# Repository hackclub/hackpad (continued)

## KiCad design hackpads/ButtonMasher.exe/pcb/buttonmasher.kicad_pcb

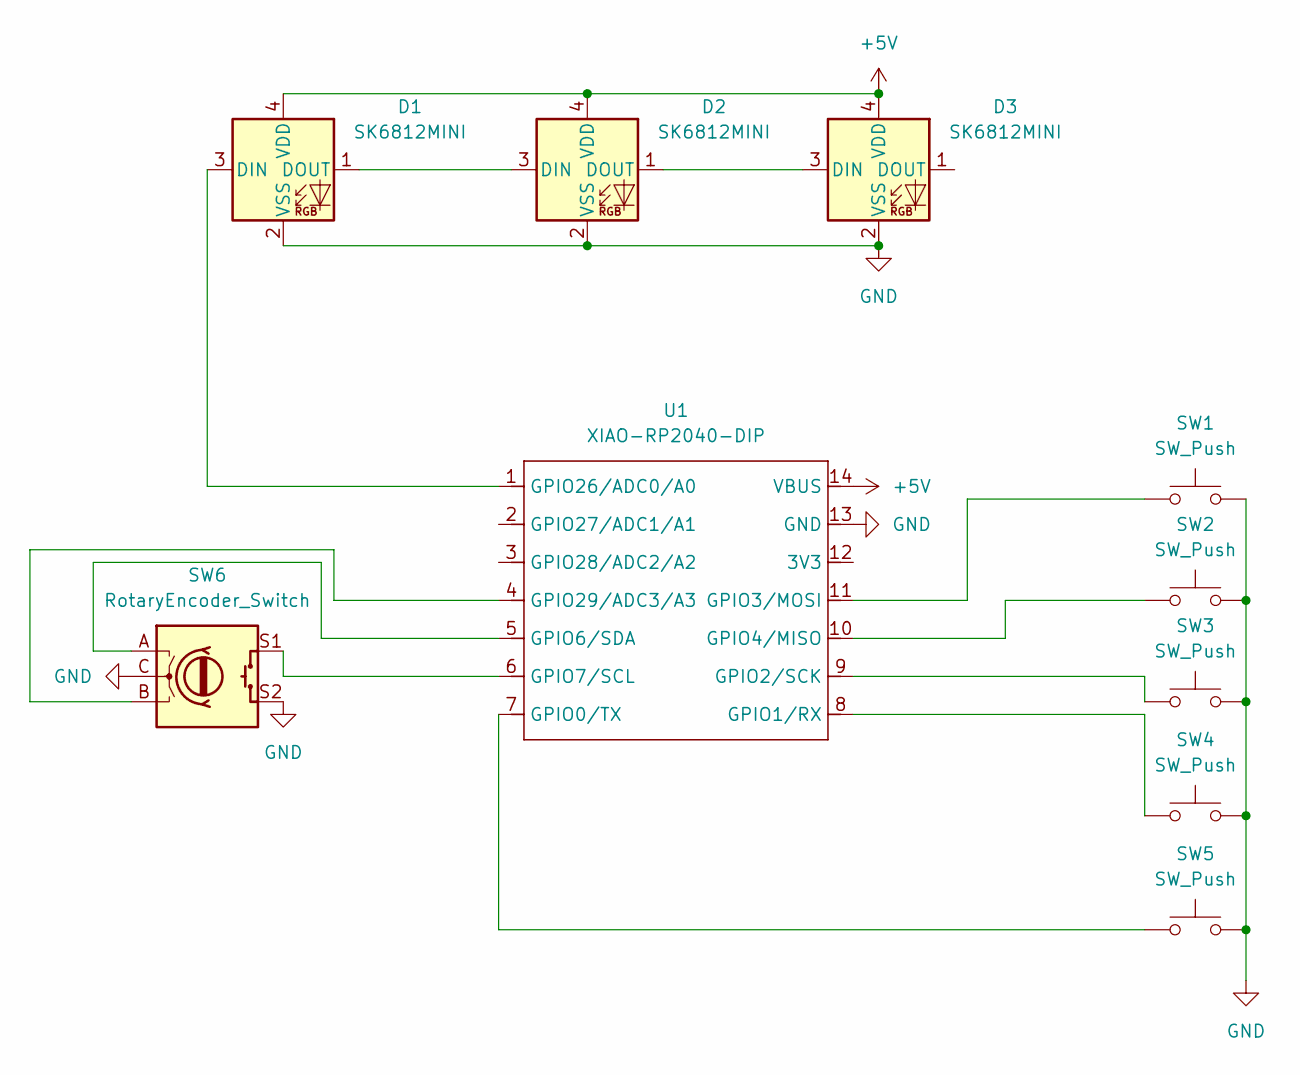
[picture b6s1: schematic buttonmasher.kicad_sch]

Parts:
D1, D2, D3: SK6812MINI; LED_SK6812MINI_PLCC4_3.5x3.5mm_P1.75mm
SW1, SW2, SW3, SW4, SW5: SW_Push; SW_Cherry_MX_1.00u_PCB
SW6: RotaryEncoder_Switch; RotaryEncoder_Alps_EC11E-Switch_Vertical_H20mm_CircularMoun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
U1: XIAO-RP2040-DIP

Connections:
+5V: D1.4 (VDD), D2.4 (VDD), D3.4 (VDD), U1.14 (VBUS)
GND: D1.2 (VSS), D2.2 (VSS), D3.2 (VSS), SW1.2, SW2.2, SW3.2, SW4.2, SW5.2, SW6.C, SW6.S2, U1.13 (GND)
unnamed: D1.3 (DIN), U1.1 (GPIO26/ADC0/A0)
unnamed: D1.1 (DOUT), D2.3 (DIN)
unnamed: D2.1 (DOUT), D3.3 (DIN)
unnamed: SW5.1, U1.7 (GPIO0/TX)
unnamed: SW4.1, U1.8 (GPIO1/RX)
unnamed: SW3.1, U1.9 (GPIO2/SCK)
unnamed: SW1.1, U1.11 (GPIO3/MOSI)
unnamed: SW2.1, U1.10 (GPIO4/MISO)
unnamed: SW6.A, U1.5 (GPIO6/SDA)
unnamed: SW6.S1, U1.6 (GPIO7/SCL)
unnamed: SW6.B, U1.4 (GPIO29/ADC3/A3)

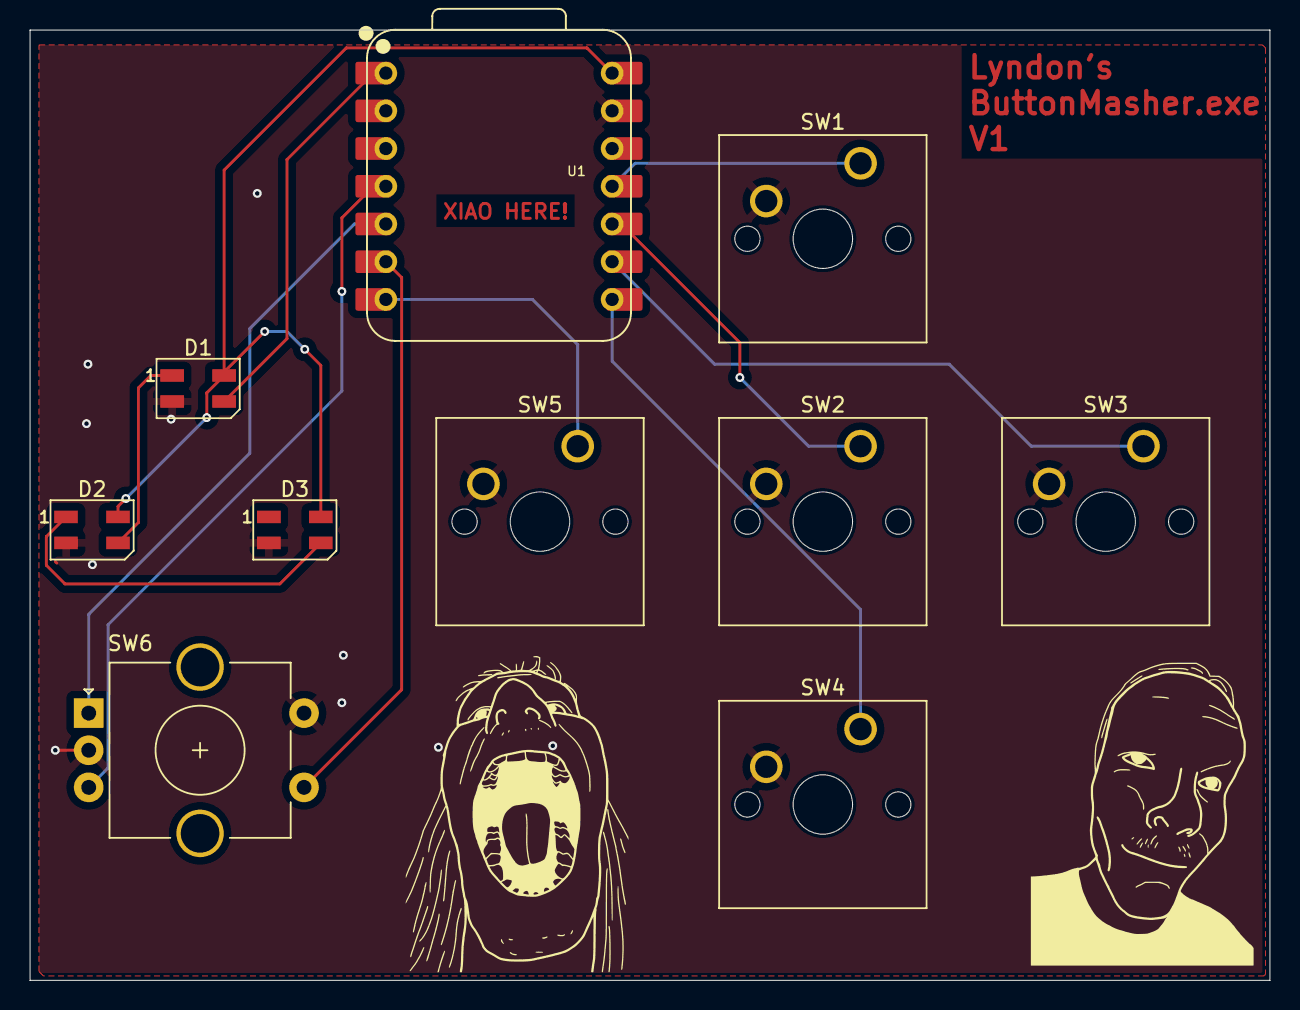
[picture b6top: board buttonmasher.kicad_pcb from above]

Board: 2 copper layers, 83.5 x 64.0 mm, 10 parts (0 on the bottom side), 13 nets.

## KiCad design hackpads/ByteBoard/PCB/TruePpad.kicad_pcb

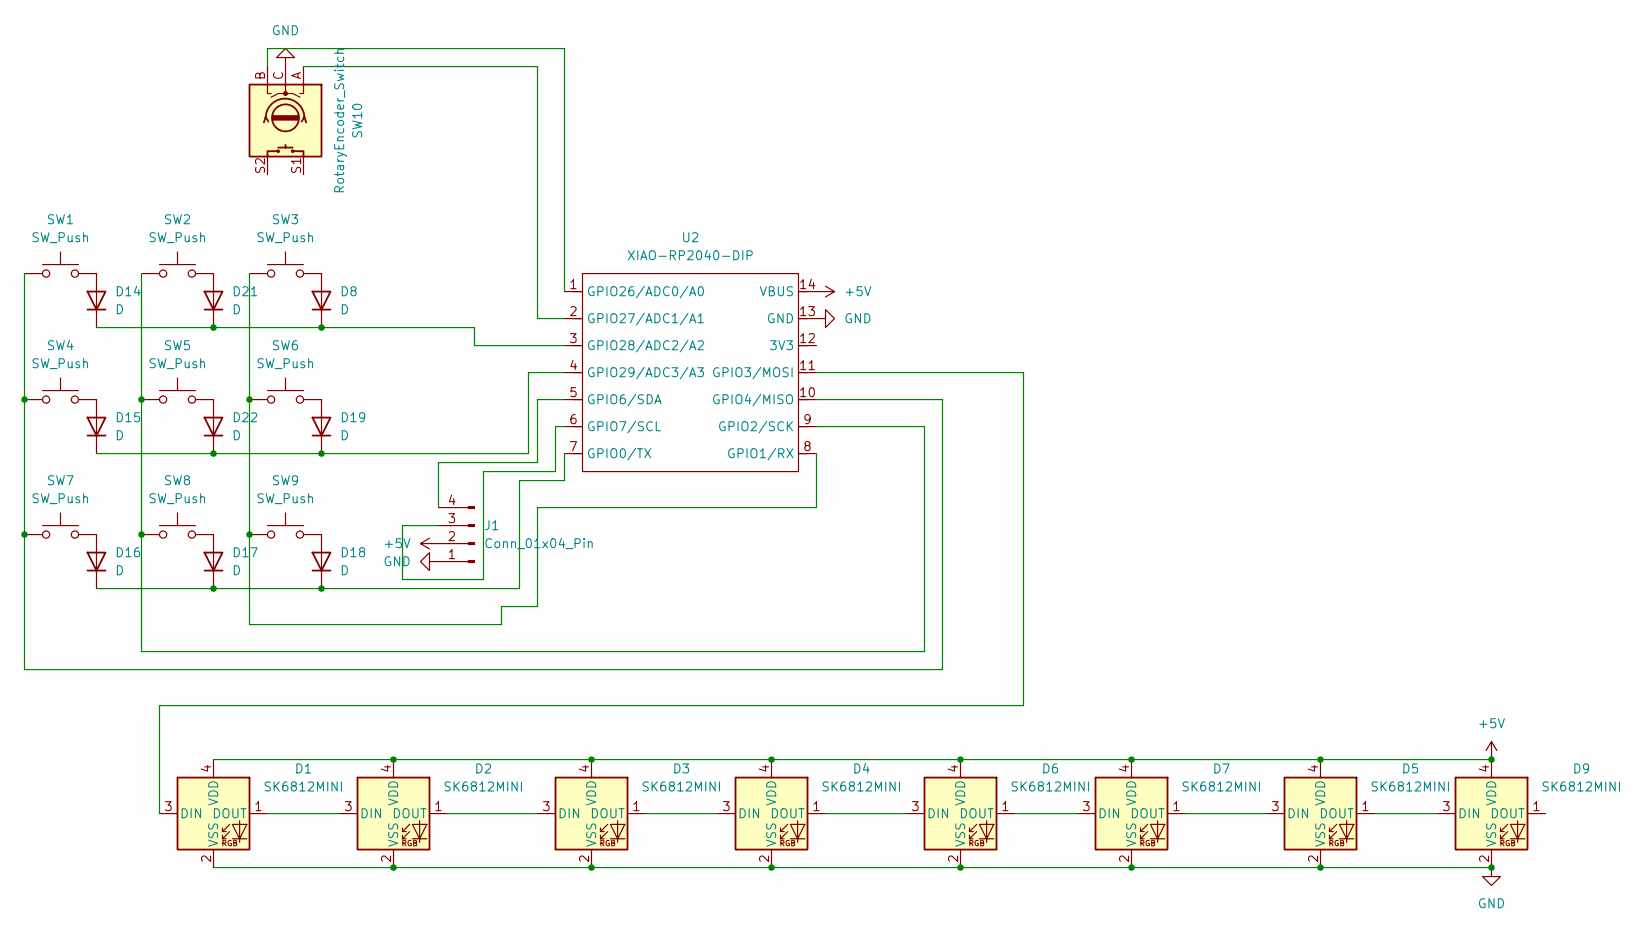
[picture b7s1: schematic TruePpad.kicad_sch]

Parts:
D1, D2, D3, D4, D5, D6, D7, D9: SK6812MINI; LED_SK6812MINI_PLCC4_3.5x3.5mm_P1.75mm
D8, D14, D15, D16, D17, D18, D19, D21, D22: D; D_DO-35_SOD27_P7.62mm_Horizontal
J1: Conn_01x04_Pin; SSD1306-0.91-OLED-4pin-128x32
SW1, SW2, SW3, SW4, SW5, SW6, SW7, SW8, SW9: SW_Push; SW_Cherry_MX_1.00u_PCB
SW10: RotaryEncoder_Switch; RotaryEncoder_Alps_EC11E-Switch_Vertical_H20mm_CircularMoun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
U2: XIAO-RP2040-DIP

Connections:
+5V: D1.4 (VDD), D2.4 (VDD), D3.4 (VDD), D4.4 (VDD), D5.4 (VDD), D6.4 (VDD), D7.4 (VDD), D9.4 (VDD), J1.2, U2.14 (VBUS)
GND: D1.2 (VSS), D2.2 (VSS), D3.2 (VSS), D4.2 (VSS), D5.2 (VSS), D6.2 (VSS), D7.2 (VSS), D9.2 (VSS), J1.1, SW10.C, U2.13 (GND)
unnamed: D1.3 (DIN), U2.11 (GPIO3/MOSI)
unnamed: D1.1 (DOUT), D2.3 (DIN)
unnamed: D2.1 (DOUT), D3.3 (DIN)
unnamed: D3.1 (DOUT), D4.3 (DIN)
unnamed: D4.1 (DOUT), D6.3 (DIN)
unnamed: D5.3 (DIN), D7.1 (DOUT)
unnamed: D5.1 (DOUT), D9.3 (DIN)
unnamed: D6.1 (DOUT), D7.3 (DIN)
unnamed: D8.2 (A), SW3.2
unnamed: D14.2 (A), SW1.2
unnamed: D8.1 (K), D14.1 (K), D21.1 (K), U2.3 (GPIO28/ADC2/A2)
unnamed: D15.2 (A), SW4.2
unnamed: D15.1 (K), D19.1 (K), D22.1 (K), U2.4 (GPIO29/ADC3/A3)
unnamed: D16.2 (A), SW7.2
unnamed: D16.1 (K), D17.1 (K), D18.1 (K), U2.7 (GPIO0/TX)
unnamed: D17.2 (A), SW8.2
unnamed: D18.2 (A), SW9.2
unnamed: D19.2 (A), SW6.2
unnamed: D21.2 (A), SW2.2
unnamed: D22.2 (A), SW5.2
unnamed: J1.3, U2.6 (GPIO7/SCL)
unnamed: J1.4, U2.5 (GPIO6/SDA)
unnamed: SW3.1, SW6.1, SW9.1, U2.8 (GPIO1/RX)
unnamed: SW2.1, SW5.1, SW8.1, U2.9 (GPIO2/SCK)
unnamed: SW1.1, SW4.1, SW7.1, U2.10 (GPIO4/MISO)
unnamed: SW10.B, U2.1 (GPIO26/ADC0/A0)
unnamed: SW10.A, U2.2 (GPIO27/ADC1/A1)

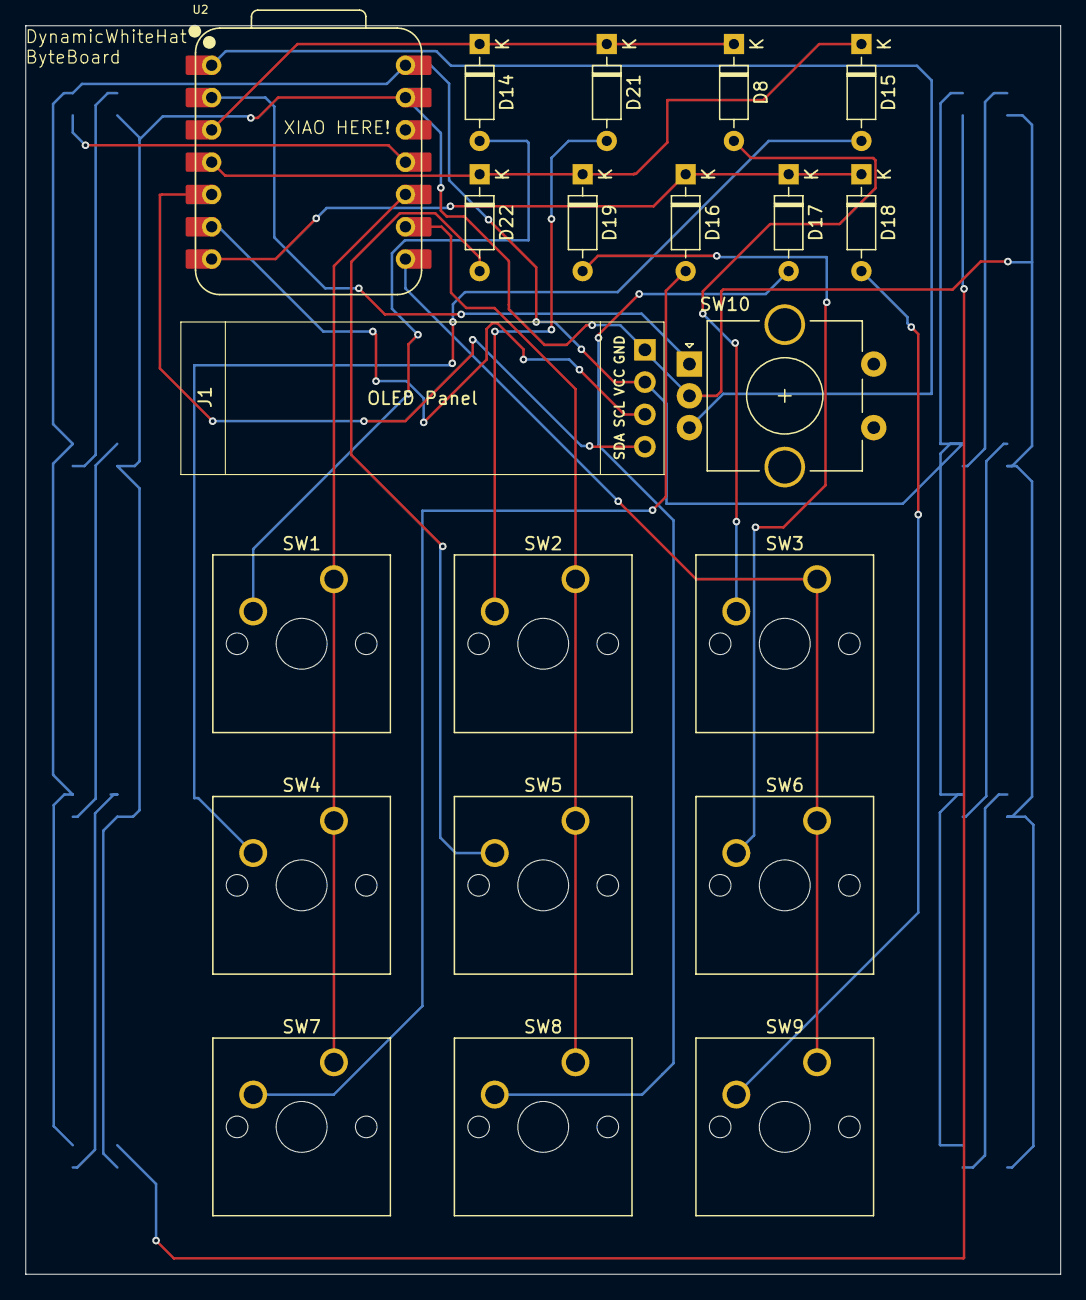
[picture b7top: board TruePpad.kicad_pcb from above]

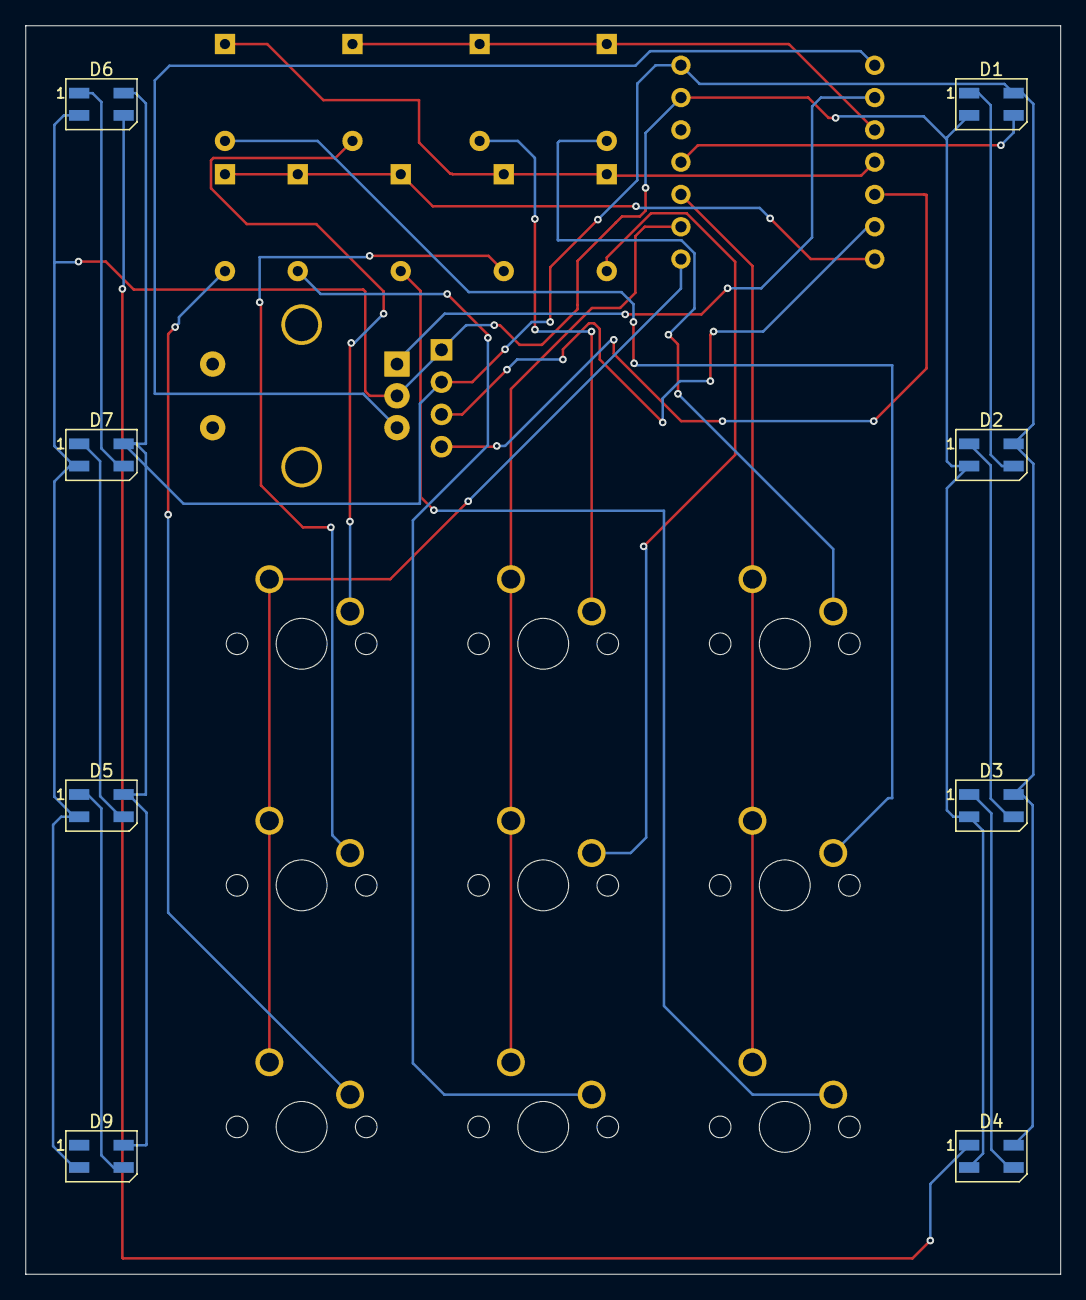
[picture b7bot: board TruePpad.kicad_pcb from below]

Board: 2 copper layers, 81.4 x 98.2 mm, 29 parts (8 on the bottom side), 29 nets.

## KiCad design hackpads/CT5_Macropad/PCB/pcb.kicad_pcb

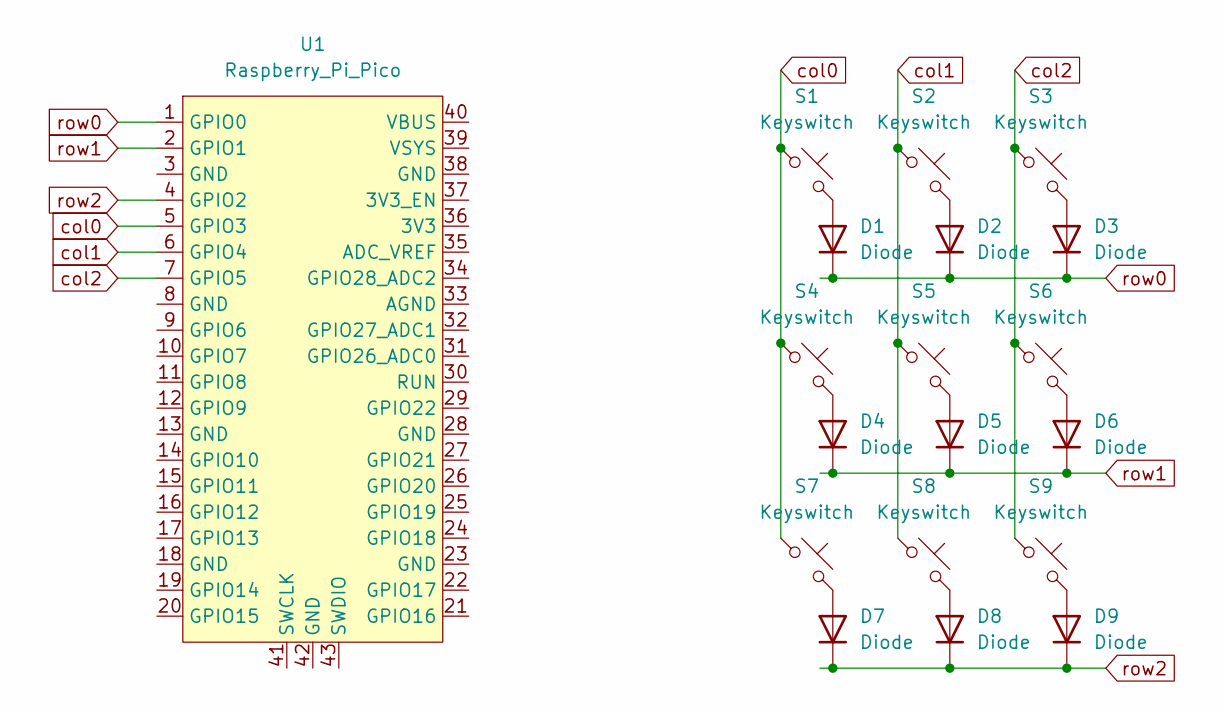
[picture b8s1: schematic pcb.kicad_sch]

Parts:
D1, D2, D3, D4, D5, D6, D7, D8, D9: Diode; Diode_DO-35
S1, S2, S3, S4, S5, S6, S7, S8, S9: Keyswitch; MX_PCB_1.00u
U1: Raspberry_Pi_Pico

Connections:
unnamed: D1.2 (A), S1.2
unnamed: D2.2 (A), S2.2
unnamed: D3.2 (A), S3.2
unnamed: D4.2 (A), S4.2
unnamed: D5.2 (A), S5.2
unnamed: D6.2 (A), S6.2
unnamed: D7.2 (A), S7.2
unnamed: D8.2 (A), S8.2
unnamed: D9.2 (A), S9.2
col0: S1.1, S4.1, S7.1, U1.5 (GPIO3)
col1: S2.1, S5.1, S8.1, U1.6 (GPIO4)
col2: S3.1, S6.1, S9.1, U1.7 (GPIO5)
row0: D1.1 (K), D2.1 (K), D3.1 (K), U1.1 (GPIO0)
row1: D4.1 (K), D5.1 (K), D6.1 (K), U1.2 (GPIO1)
row2: D7.1 (K), D8.1 (K), D9.1 (K), U1.4 (GPIO2)

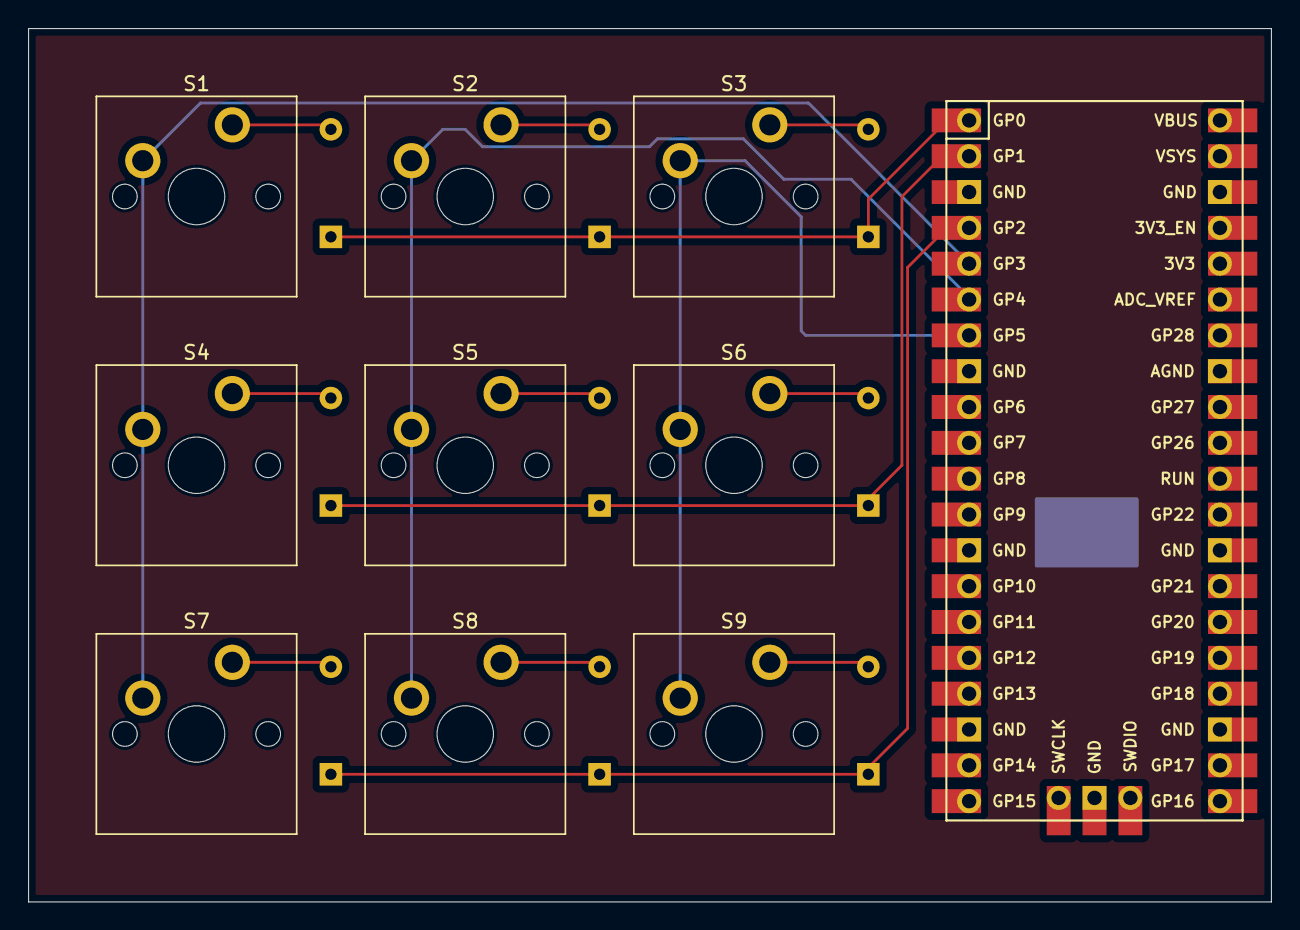
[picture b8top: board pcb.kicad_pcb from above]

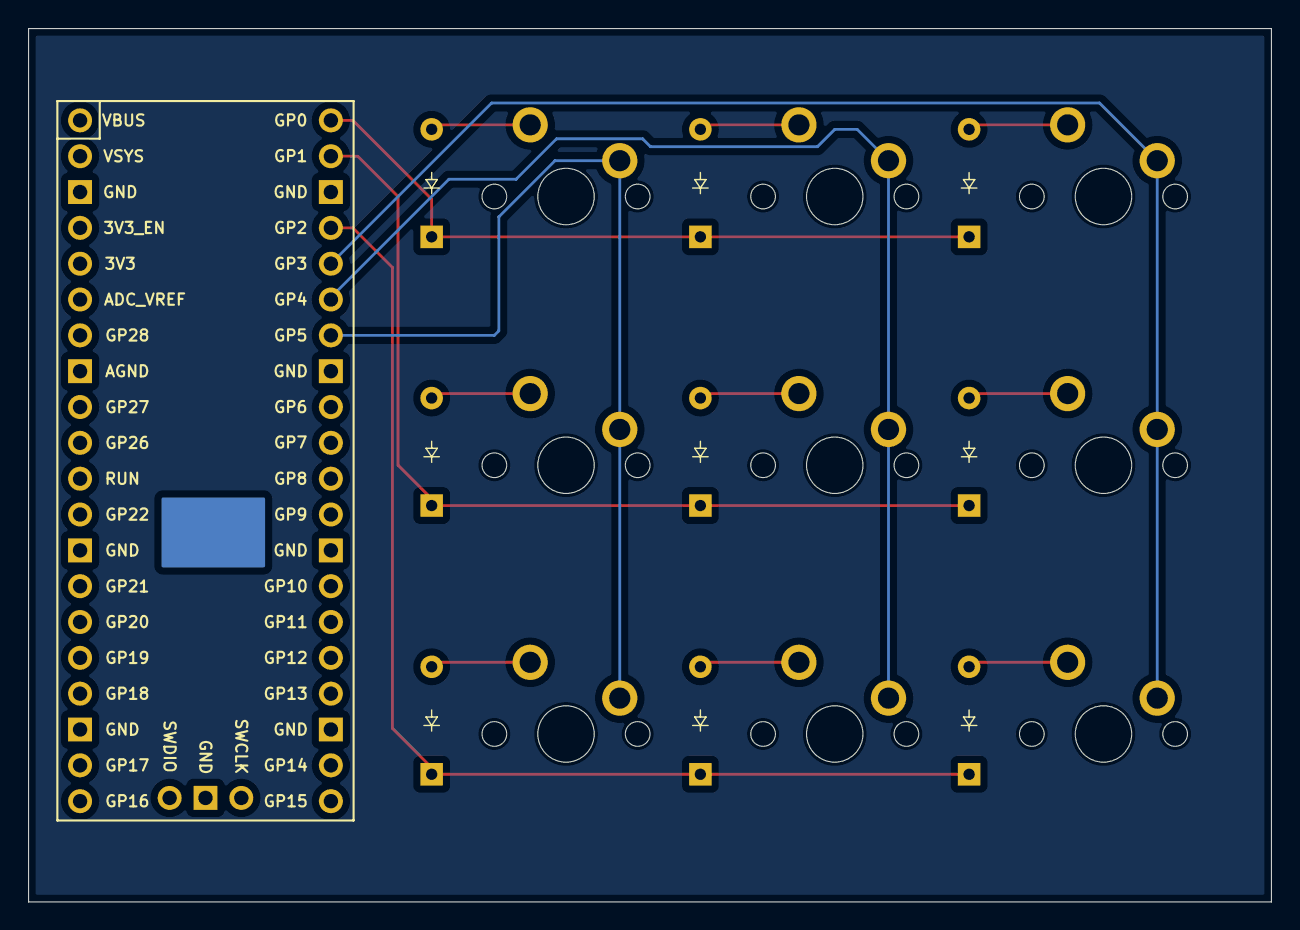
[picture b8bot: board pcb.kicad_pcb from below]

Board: 2 copper layers, 88.1 x 61.9 mm, 19 parts (9 on the bottom side), 15 nets.

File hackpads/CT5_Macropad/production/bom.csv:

Designator,Footprint,Quantity,Value,LCSC Part #
"D1, D2, D3, D4, D5, D6, D7, D8, D9",Diode_DO-35,9,Diode,
"S1, S2, S3, S4, S5, S6, S7, S8, S9",MX_PCB_1.00u,9,Keyswitch,
U1,Raspberry_Pi_Pico,1,Raspberry_Pi_Pico,
